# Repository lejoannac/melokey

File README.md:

# melokey
A midi keyboard designed with the purpose of educating neurodivergent students and providing them with a pathway to music 

# features
- High contrast, large keys to aid in student's comfort
- Immediate visual feedback through light-up keys
- Visual and auditory prompts to assist learning chords, scales, and songs
- Companion iPad app that makes making-making an easy and enjoyable experience!

# CAD Model

# PCB Design

# Schematic

# App design

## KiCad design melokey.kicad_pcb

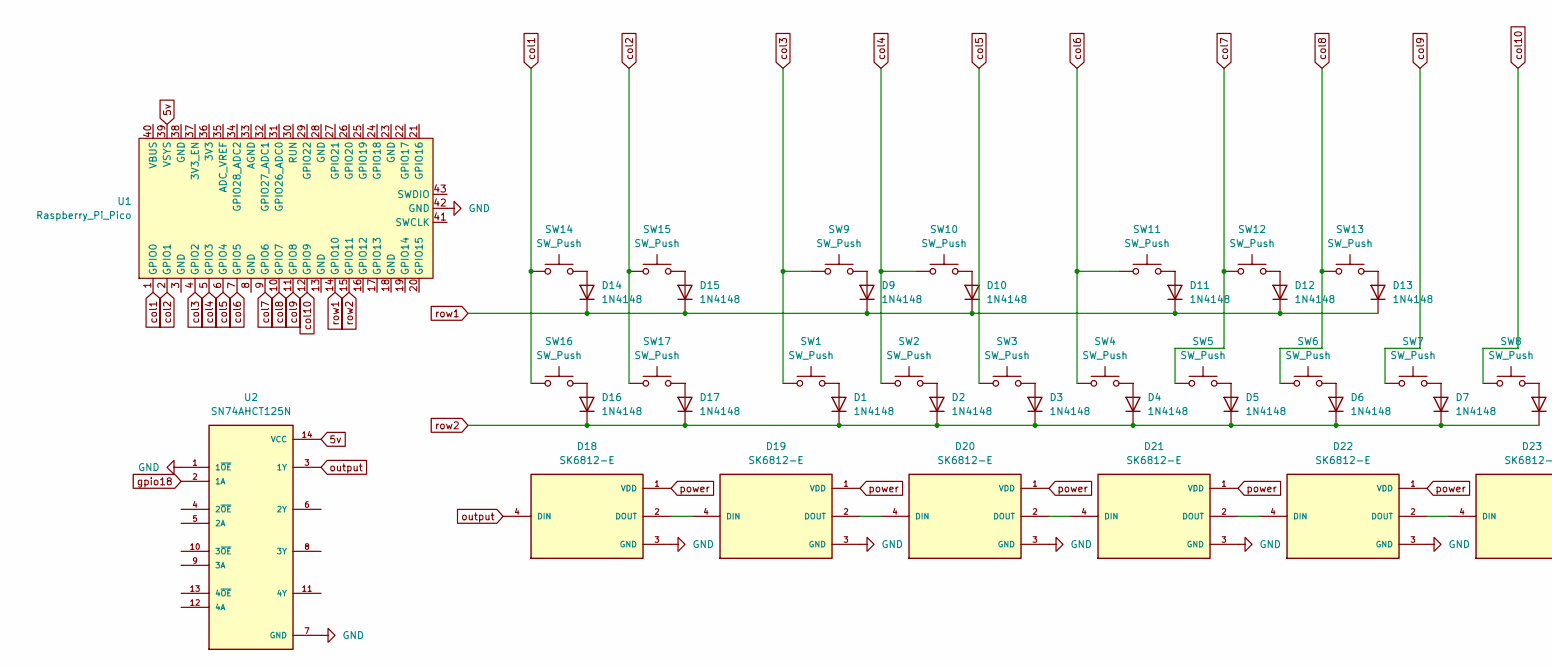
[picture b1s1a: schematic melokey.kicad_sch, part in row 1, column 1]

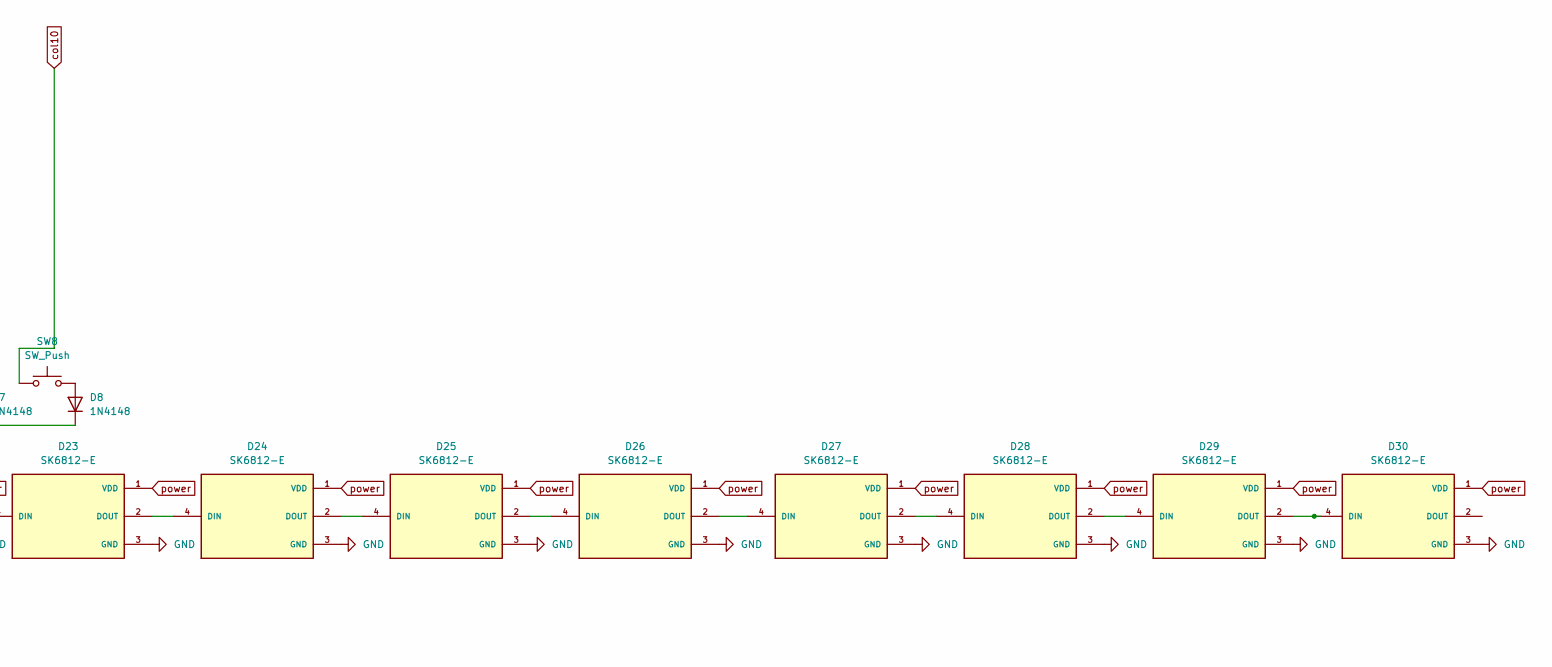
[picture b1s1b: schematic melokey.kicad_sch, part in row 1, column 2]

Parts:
D1, D2, D3, D4, D5, D6, D7, D8, D9, D10, D11, D12, D13, D14, D15, D16, D17: 1N4148; D_DO-35_SOD27_P7.62mm_Horizontal
D18, D19, D20, D21, D22, D23, D24, D25, D26, D27, D28, D29, D30: SK6812-E; LED_SK6812-Eneww; PARTREV 2
SW1, SW2, SW3, SW4, SW5, SW6, SW7, SW8, SW9, SW10, SW11, SW12, SW13: SW_Push; MX_PCB_3.00u_90degnew
SW14, SW15, SW16, SW17: SW_Push; MX_PCB_1.00unew
U1: Raspberry_Pi_Pico
U2: SN74AHCT125N; DIP794W45P254L1930H508Q14; PARTREV Q

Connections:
5v: U1.39 (VSYS), U2.14 (VCC)
GND: D18.3 (GND), D19.3 (GND), D20.3 (GND), D21.3 (GND), D22.3 (GND), D23.3 (GND), D24.3 (GND), D25.3 (GND), D26.3 (GND), D27.3 (GND), D28.3 (GND), D29.3 (GND), D30.3 (GND), U1.42 (GND), U2.1 (1~OE), U2.7 (GND)
unnamed: D1.2 (A), SW1.2
unnamed: D2.2 (A), SW2.2
unnamed: D3.2 (A), SW3.2
unnamed: D4.2 (A), SW4.2
unnamed: D5.2 (A), SW5.2
unnamed: D6.2 (A), SW6.2
unnamed: D7.2 (A), SW7.2
unnamed: D8.2 (A), SW8.2
unnamed: D9.2 (A), SW9.2
unnamed: D10.2 (A), SW10.2
unnamed: D11.2 (A), SW11.2
unnamed: D12.2 (A), SW12.2
unnamed: D13.2 (A), SW13.2
unnamed: D14.2 (A), SW14.2
unnamed: D15.2 (A), SW15.2
unnamed: D16.2 (A), SW16.2
unnamed: D17.2 (A), SW17.2
unnamed: D18.2 (DOUT), D19.4 (DIN)
unnamed: D19.2 (DOUT), D20.4 (DIN)
unnamed: D20.2 (DOUT), D21.4 (DIN)
unnamed: D21.2 (DOUT), D22.4 (DIN)
unnamed: D22.2 (DOUT), D23.4 (DIN)
unnamed: D23.2 (DOUT), D24.4 (DIN)
unnamed: D24.2 (DOUT), D25.4 (DIN)
unnamed: D25.2 (DOUT), D26.4 (DIN)
unnamed: D26.2 (DOUT), D27.4 (DIN)
unnamed: D27.2 (DOUT), D28.4 (DIN)
unnamed: D28.2 (DOUT), D29.4 (DIN)
unnamed: D29.2 (DOUT), D30.4 (DIN)
col1: SW14.1, SW16.1, U1.1 (GPIO0)
col2: SW15.1, SW17.1, U1.2 (GPIO1)
col3: SW1.1, SW9.1, U1.4 (GPIO2)
col4: SW2.1, SW10.1, U1.5 (GPIO3)
col5: SW3.1, U1.6 (GPIO4)
col6: SW4.1, SW11.1, U1.7 (GPIO5)
col7: SW5.1, SW12.1, U1.9 (GPIO6)
col8: SW6.1, SW13.1, U1.10 (GPIO7)
col9: SW7.1, U1.11 (GPIO8)
col10: SW8.1, U1.12 (GPIO9)
gpio18: U2.2 (1A)
output: D18.4 (DIN), U2.3 (1Y)
power: D18.1 (VDD), D19.1 (VDD), D20.1 (VDD), D21.1 (VDD), D22.1 (VDD), D23.1 (VDD), D24.1 (VDD), D25.1 (VDD), D26.1 (VDD), D27.1 (VDD), D28.1 (VDD), D29.1 (VDD), D30.1 (VDD)
row1: D9.1 (K), D10.1 (K), D11.1 (K), D12.1 (K), D13.1 (K), D14.1 (K), D15.1 (K), U1.14 (GPIO10)
row2: D1.1 (K), D2.1 (K), D3.1 (K), D4.1 (K), D5.1 (K), D6.1 (K), D7.1 (K), D8.1 (K), D16.1 (K), D17.1 (K), U1.15 (GPIO11)

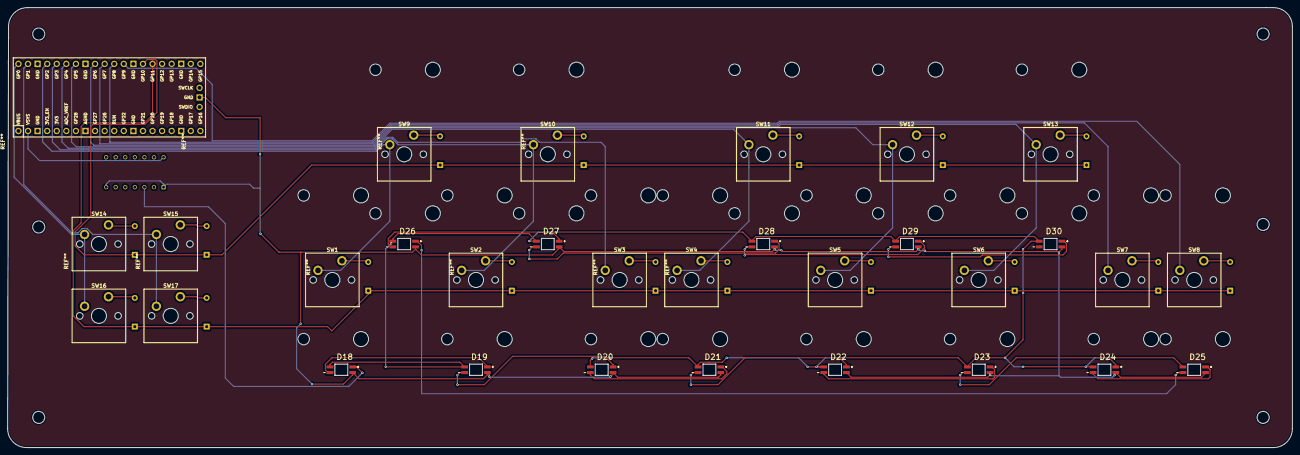
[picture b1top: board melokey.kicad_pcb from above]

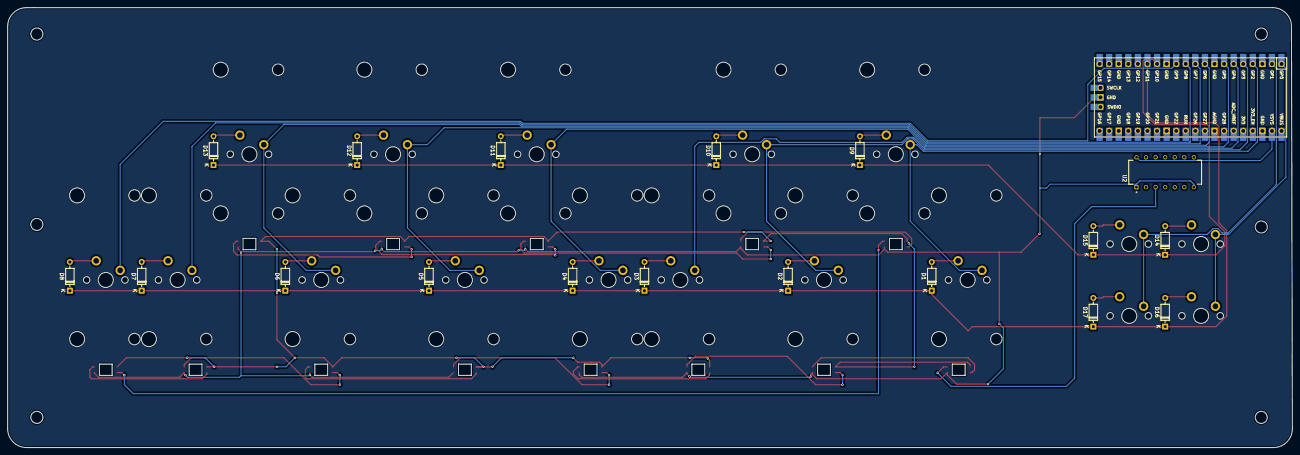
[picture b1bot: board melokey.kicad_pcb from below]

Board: 2 copper layers, 340.8 x 116.7 mm, 49 parts (19 on the bottom side), 45 nets.

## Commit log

2024-07-08 Gerber Files
2024-07-08 Kicad Files
2024-08-05 3d printing files
2024-08-11 figma file
2025-12-28 Add design images to README
    Added images for CAD model, PCB design, schematic, and app design.
